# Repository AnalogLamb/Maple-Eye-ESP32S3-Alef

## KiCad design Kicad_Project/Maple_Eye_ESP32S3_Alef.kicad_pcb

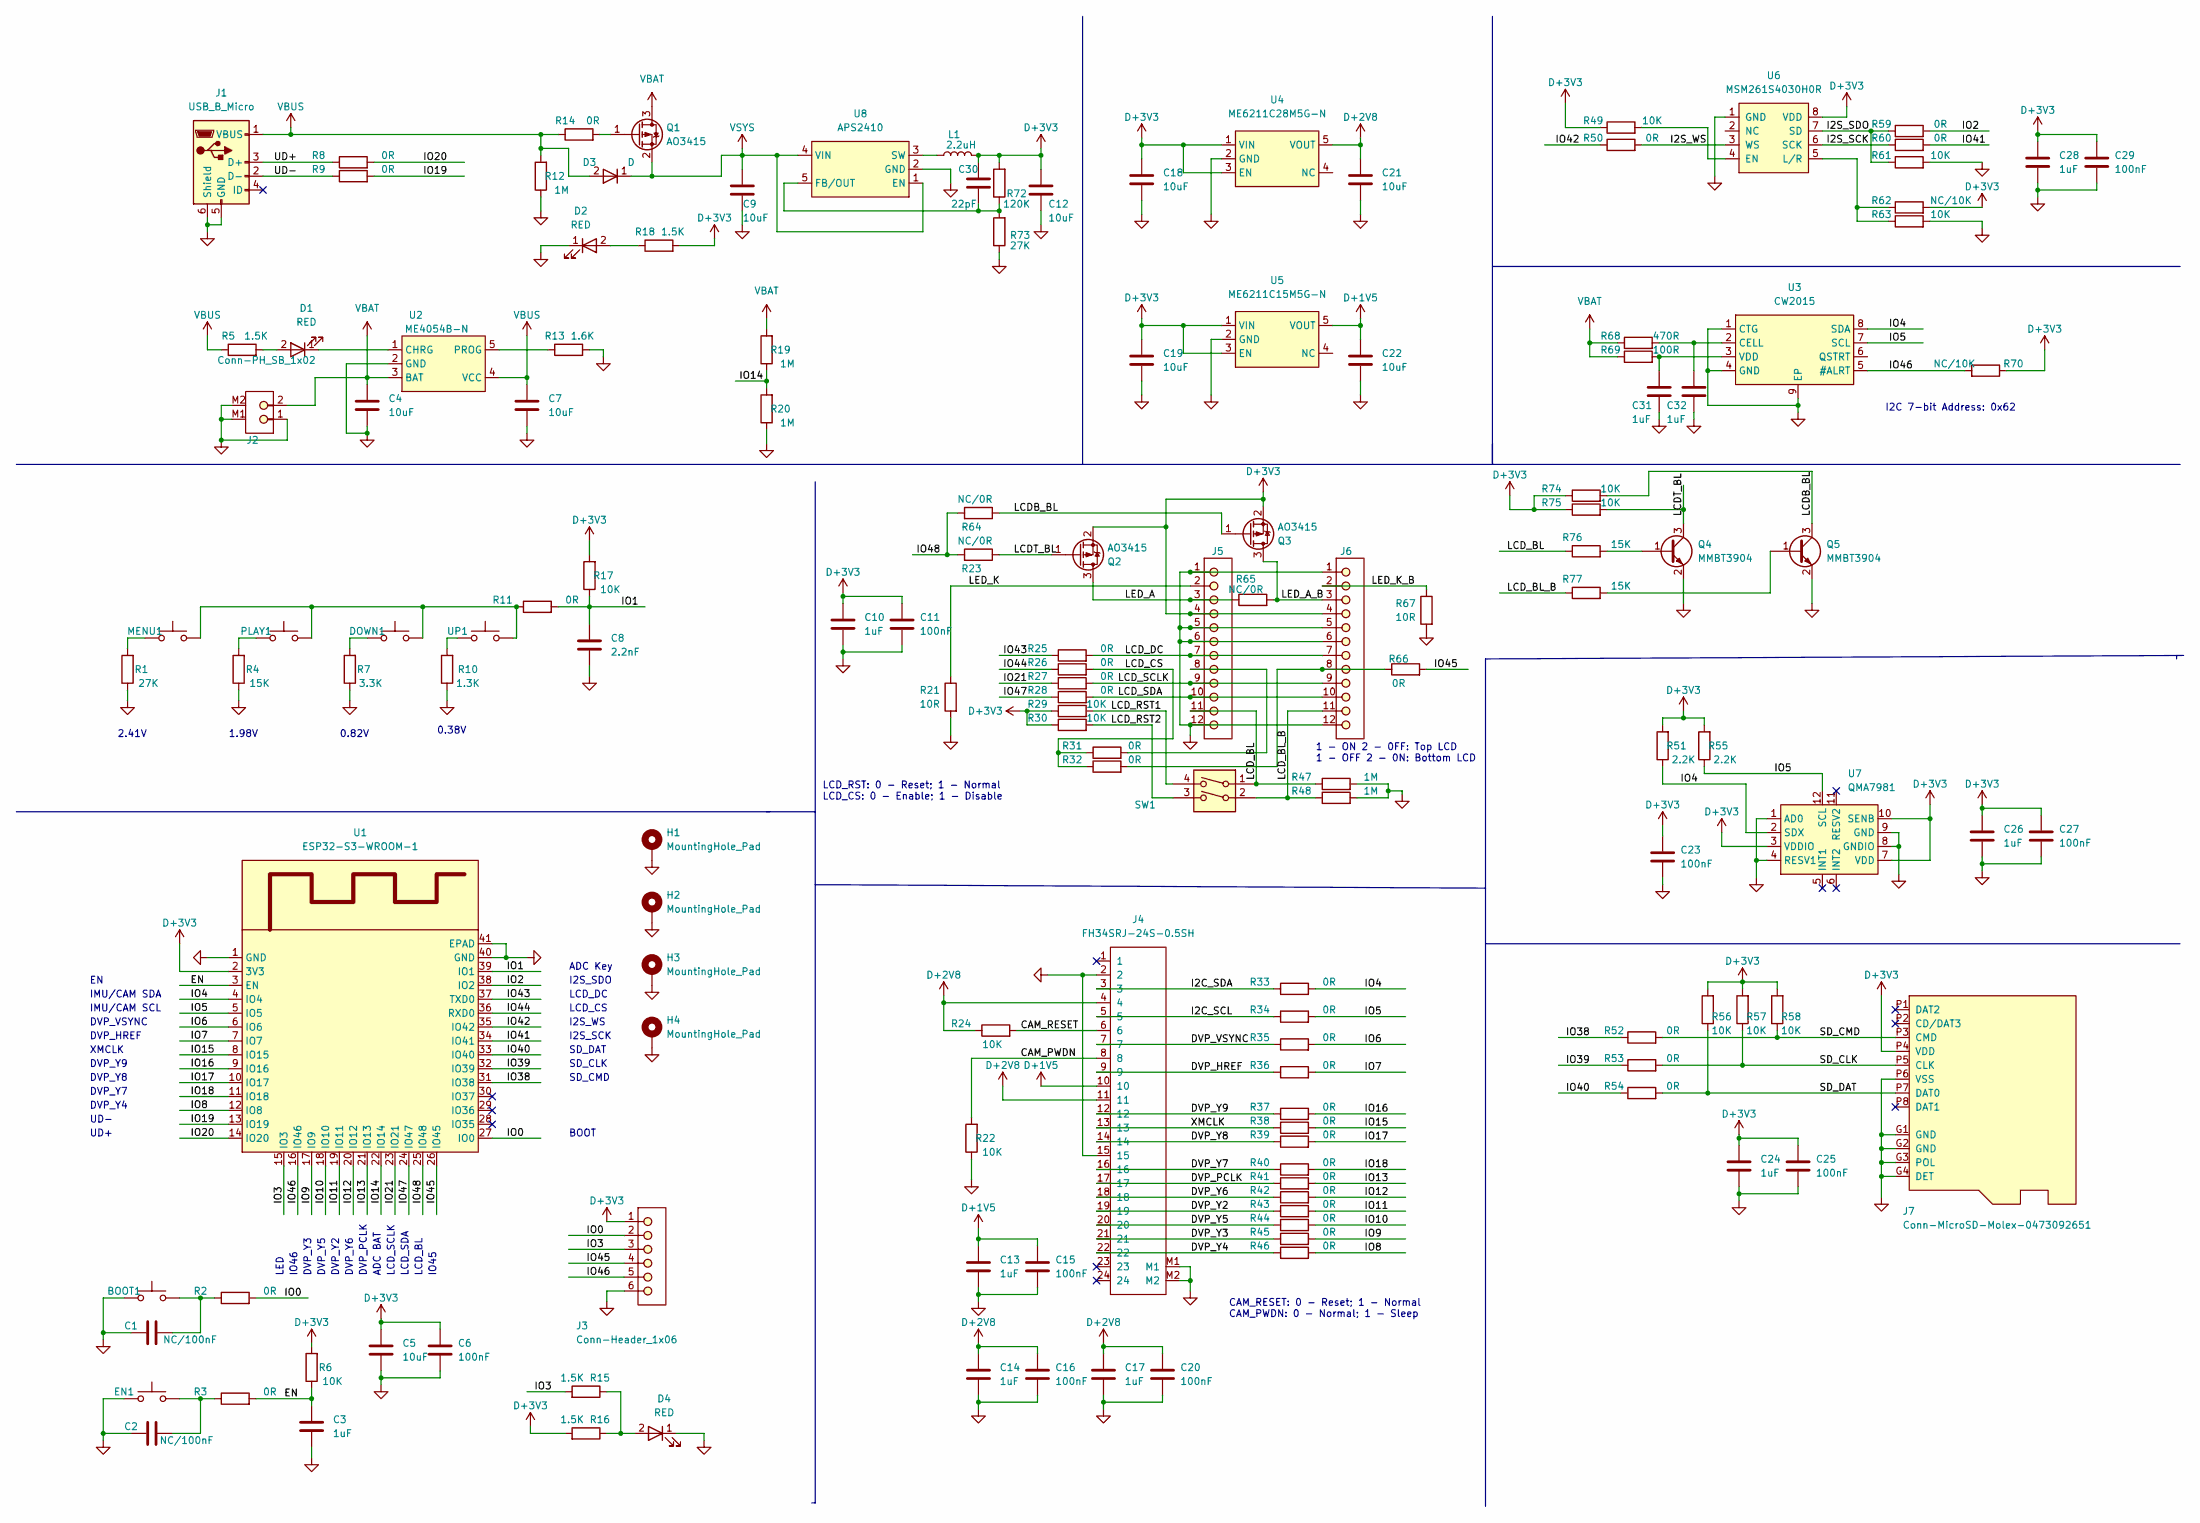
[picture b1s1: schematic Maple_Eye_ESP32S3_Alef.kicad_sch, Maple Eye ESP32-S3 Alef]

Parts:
BOOT1: SW_Push; PB_3x4MM_2P
C1, C2: NC/100nF; 0402C
C3, C10, C13, C14, C17, C24, C26, C28, C31, C32: 1uF; 0402C
C4, C5, C7, C9, C12, C18, C19, C21, C22: 10uF; 0402C
C6, C11, C15, C16, C20, C23, C25, C27, C29: 100nF; 0402C
C8: 2.2nF; 0402C
C30: 22pF; 0402C
D1, D2, D4: RED; 0402D
D3: D; SOD-123
DOWN1: SW_Push; PB_3X4MM_2P_HS
EN1: SW_Push; PB_3x4MM_2P
H1, H2, H3, H4: MountingHole_Pad; MountingHole_2.2mm_M2_Pad_Via
J1: USB_B_Micro; MICRO-USB5+4P-SMD-0.65-B
J2: Conn-PH_SB_1x02; S2B-PH
J3: Conn-Header_1x06; 1X06
J4: FH34SRJ-24S-0.5SH; Conn-FPC-HRS-FH34SRJ-24S-0.5SH
J5, J6: Conn-Header_1x12; LCD_1.3_SPI
J7: Conn-MicroSD-Molex-0473092651
L1: 2.2uH; L_1008_2520Metric
MENU1: SW_Push; PB_3X4MM_2P_HS
PLAY1: SW_Push; PB_3X4MM_2P_HS
Q1, Q2, Q3: AO3415; SOT23-3
Q4, Q5: MMBT3904; SOT23-3
R1, R73: 27K; 0402R
R2, R3, R8, R9, R11, R14, R25, R26, R27, R28, R31, R32, R33, R34, R35, R36, R37, R38, R39, R40, R41, R42, R43, R44, R45, R46, R50, R52, R53, R54, R59, R60, R66: 0R; 0402R
R4, R76, R77: 15K; 0402R
R5, R15, R16, R18: 1.5K; 0402R
R6, R17, R22, R24, R29, R30, R49, R56, R57, R58, R61, R63, R74, R75: 10K; 0402R
R7: 3.3K; 0402R
R10: 1.3K; 0402R
R12, R19, R20, R47, R48: 1M; 0402R
R13: 1.6K; 0402R
R21, R67: 10R; 0603
R23, R64, R65: NC/0R; 0402R
R51, R55: 2.2K; 0402R
R62, R70: NC/10K; 0402R
R68: 470R; 0402R
R69: 100R; 0402R
R72: 120K; 0402R
SW1: SW_DIP_x02; CHS-02B
U1: ESP32-S3-WROOM-1
U2: ME4054B-N; SOT23-5
U3: CW2015; TDFN-8-1EP_3x2mm_P0.5mm_EP1.4x1.4mm
U4: ME6211C28M5G-N; SOT23-5
U5: ME6211C15M5G-N; SOT23-5
U6: MSM261S4030H0R
U7: QMA7981; LGA-12_2x2mm_P0.5mm
U8: APS2410; SOT23-5
UP1: SW_Push; PB_3X4MM_2P_HS

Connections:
+1V5: C13.1, C15.1, C22.1, J4.10, U5.5 (VOUT)
+2V8: C14.1, C16.1, C17.1, C20.1, C21.1, J4.4, J4.11, R24.1, U4.5 (VOUT)
+3V3: C5.1, C6.1, C10.1, C11.1, C12.1, C18.1, C19.1, C23.1, C24.1, C25.1, C26.1, C27.1, C28.1, C29.1, C30.1, J3.1, J5.4, J6.4, J7.P4 (VDD), L1.2, Q2.2 (S), Q3.2 (S), R6.2, R16.2, R17.2, R18.2, R29.1, R30.1, R49.1, R51.2, R55.2, R56.2, R57.2, R58.2, R62.2, R70.1, R72.2, R74.1, R75.1, U1.2 (3V3), U4.1 (VIN), U4.3 (EN), U5.1 (VIN), U5.3 (EN), U6.8 (VDD), U7.3 (VDDIO), U7.7 (VDD), U7.10 (SENB)
/CAM_PWDN: J4.8, R22.2
/CAM_RESET: J4.6, R24.2
/DVP_HREF: J4.9, R36.1
/DVP_PCLK: J4.17, R41.1
/DVP_VSYNC: J4.7, R35.1
/DVP_Y2: J4.19, R43.1
/DVP_Y3: J4.21, R45.1
/DVP_Y4: J4.22, R46.1
/DVP_Y5: J4.20, R44.1
/DVP_Y6: J4.18, R42.1
/DVP_Y7: J4.16, R40.1
/DVP_Y8: J4.14, R39.1
/DVP_Y9: J4.12, R37.1
/EN: C3.1, R3.2, R6.1, U1.3 (EN)
/I2C_SCL: J4.5, R34.1
/I2C_SDA: J4.3, R33.1
/I2S_SCK: R60.1, U6.6 (SCK)
/I2S_SDO: R59.1, R61.1, U6.7 (SD)
/I2S_WS: R50.2, U6.3 (WS)
/IO0: J3.2, R2.2, U1.27 (IO0)
/IO1: C8.1, R11.2, R17.1, U1.39 (IO1)
/IO2: R59.2, U1.38 (IO2)
/IO3: J3.3, R15.2, U1.15 (IO3)
/IO4: R33.2, R51.1, U1.4 (IO4), U3.8 (SDA), U7.2 (SDX)
/IO5: R34.2, R55.1, U1.5 (IO5), U3.7 (SCL), U7.12 (SCL)
/IO6: R35.2, U1.6 (IO6)
/IO7: R36.2, U1.7 (IO7)
/IO8: R46.2, U1.12 (IO8)
/IO9: R45.2, U1.17 (IO9)
/IO10: R44.2, U1.18 (IO10)
/IO11: R43.2, U1.19 (IO11)
/IO12: R42.2, U1.20 (IO12)
/IO13: R41.2, U1.21 (IO13)
/IO14: R19.1, R20.2, U1.22 (IO14)
/IO15: R38.2, U1.8 (IO15)
/IO16: R37.2, U1.9 (IO16)
/IO17: R39.2, U1.10 (IO17)
/IO18: R40.2, U1.11 (IO18)
/IO19: R9.2, U1.13 (IO19)
/IO20: R8.2, U1.14 (IO20)
/IO21: R27.1, U1.23 (IO21)
/IO38: R52.1, U1.31 (IO38)
/IO39: R53.1, U1.32 (IO39)
/IO40: R54.1, U1.33 (IO40)
/IO41: R60.2, U1.34 (IO41)
/IO42: R50.1, U1.35 (IO42)
/IO43: R25.1, U1.37 (TXD0)
/IO44: R26.1, U1.36 (RXD0)
/IO45: J3.4, R66.2, U1.26 (IO45)
/IO46: J3.5, R70.2, U1.16 (IO46), U3.5 (#ALRT)
/IO47: R28.1, U1.24 (IO47)
/IO48: R23.2, R64.2, U1.25 (IO48)
/LCDB_BL: Q3.1 (G), Q5.3 (C), R64.1, R74.2
/LCDT_BL: Q2.1 (G), Q4.3 (C), R23.1, R75.2
/LCD_BL: J5.11, R47.1, R76.1, SW1.1
/LCD_BL_B: J6.11, R48.1, R77.1, SW1.2
/LCD_CS: R26.2, R31.1, R32.1
/LCD_DC: J5.7, J6.7, R25.2
/LCD_RST1: R29.2, SW1.4
/LCD_RST2: R30.2, SW1.3
/LCD_SCLK: J5.9, J6.9, R27.2
/LCD_SDA: J5.10, J6.10, R28.2
/LED_A: J5.3, Q2.3 (D), R65.1
/LED_A_B: J6.3, Q3.3 (D), R65.2
/LED_K: J5.2, R21.1
/LED_K_B: J6.2, R67.1
/SD_CLK: J7.P5 (CLK), R53.2, R57.1
/SD_CMD: J7.P3 (CMD), R52.2, R58.1
/SD_DAT: J7.P7 (DAT0), R54.2, R56.1
/UD+: J1.3 (D+), R8.1
/UD-: J1.2 (D-), R9.1
/XMCLK: J4.13, R38.1
GND: BOOT1.1, C1.1, C2.1, C3.2, C4.2, C5.2, C6.2, C7.2, C8.2, C9.2, C10.2, C11.2, C12.2, C13.2, C14.2, C15.2, C16.2, C17.2, C18.2, C19.2, C20.2, C21.2, C22.2, C23.2, C24.2, C25.2, C26.2, C27.2, C28.2, C29.2, C31.2, C32.2, D2.1 (K), D4.1 (K), EN1.1, H1.1, H2.1, H3.1, H4.1, J1.5 (GND), J1.6 (Shield), J2.1, J2.M1, J2.M2, J3.6, J4.2, J4.15, J4.M1, J4.M2, J5.1, J5.5, J5.6, J5.12, J6.1, J6.5, J6.6, J6.12, J7.G1 (GND), J7.G2 (GND), J7.G3 (POL), J7.G4 (DET), J7.P6 (VSS), Q4.2 (E), Q5.2 (E), R1.1, R4.1, R7.1, R10.1, R12.1, R13.2, R20.1, R21.2, R22.1, R47.2, R48.2, R61.2, R63.2, R67.2, R73.1, U1.1 (GND), U1.40 (GND), U1.41 (EPAD), U2.2 (GND), U3.1 (CTG), U3.4 (GND), U3.9 (EP), U4.2 (GND), U5.2 (GND), U6.1 (GND), U7.1 (AD0), U7.4 (RESV1), U7.8 (GNDIO), U7.9 (GND), U8.2 (GND)
unnamed: BOOT1.2, C1.2, R2.1
unnamed: C2.2, EN1.2, R3.1
unnamed: C30.2, R72.1, R73.2, U8.5 (FB/OUT)
unnamed: C31.1, R69.2, U3.3 (VDD)
unnamed: C32.1, R68.2, U3.2 (CELL)
unnamed: D1.1 (K), U2.1 (CHRG)
unnamed: D1.2 (A), R5.2
unnamed: D2.2 (A), R18.1
unnamed: D4.2 (A), R15.1, R16.1
unnamed: DOWN1.1, R7.2
unnamed: DOWN1.2, MENU1.2, PLAY1.2, R11.1, UP1.2
unnamed: J5.8, R31.2
unnamed: J6.8, R32.2, R66.1
unnamed: L1.1, U8.3 (SW)
unnamed: MENU1.1, R1.2
unnamed: PLAY1.1, R4.2
unnamed: Q1.1 (G), R14.2
unnamed: Q4.1 (B), R76.2
unnamed: Q5.1 (B), R77.2
unnamed: R10.2, UP1.1
unnamed: R13.1, U2.5 (PROG)
unnamed: R49.2, U6.4 (EN)
unnamed: R62.1, R63.1, U6.5 (L/R)
VBAT: C4.1, J2.2, Q1.3 (D), R19.2, R68.1, R69.1, U2.3 (BAT)
VBUS: C7.1, D3.2 (A), J1.1 (VBUS), R5.1, R12.2, R14.1, U2.4 (VCC)
VSYS: C9.1, D3.1 (K), Q1.2 (S), U8.1 (EN), U8.4 (VIN)

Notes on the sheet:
DVP_VSYNC
SD_CMD
DVP_Y9
DVP_Y7
DVP_Y4
LCD_DC
0.38V
UD+
1 - ON 2 - 0FF: Top LCD 1 - OFF 2 - 0N: Bottom LCD
BOOT
DVP_HREF
DVP_Y6
DVP_Y8
1.98V
LCD_BL
LCD_SCLK
2.41V
IMU/CAM SCL
CAM_RESET: 0 - Reset; 1 - Normal CAM_PWDN: 0 - Normal; 1 - Sleep
DVP_Y3
DVP_Y2
UD-
DVP_Y5
IO45
I2C 7-bit Address: 0x62
0.82V
SD_CLK
I2S_WS
XMCLK
ADC Key
LED
LCD_RST: 0 - Reset; 1 - Normal LCD_CS: 0 - Enable; 1 - Disable
I2S_SCK
DVP_PCLK
LCD_CS
LCD_SDA
ADC BAT
IMU/CAM SDA
I2S_SDO
IO46

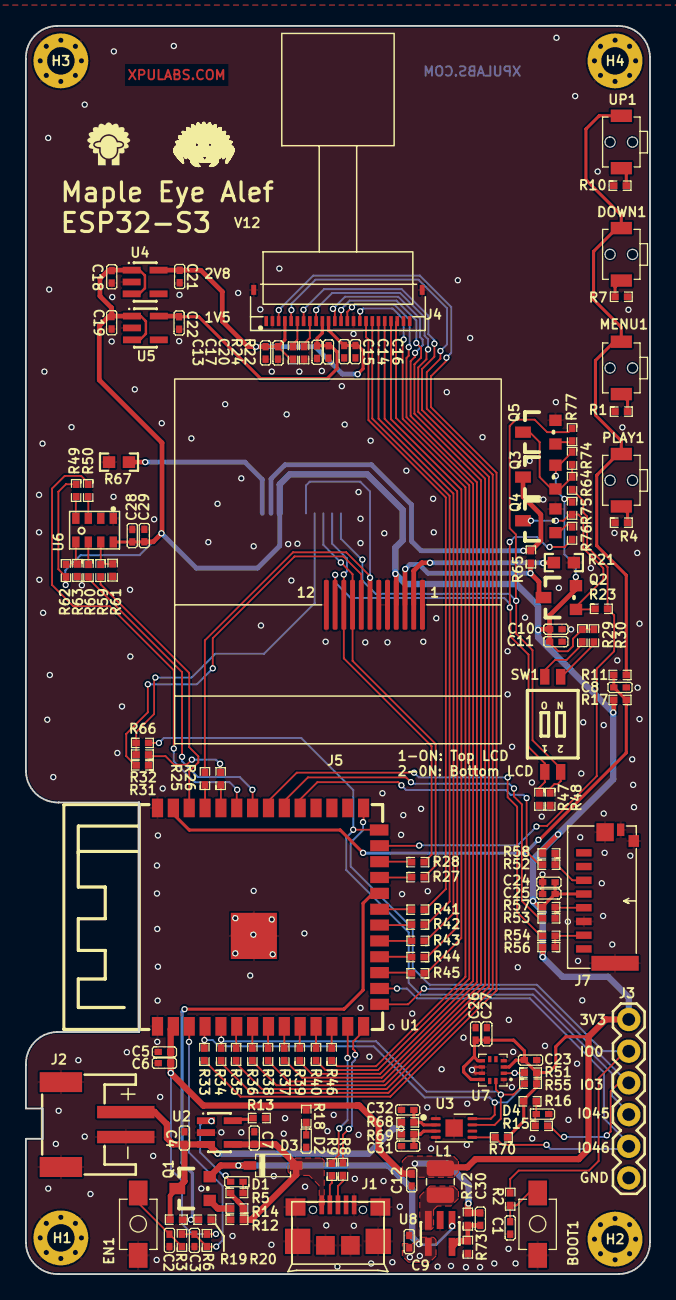
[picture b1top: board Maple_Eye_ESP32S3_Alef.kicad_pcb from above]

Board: 2 copper layers, 50.0 x 100.0 mm, 144 parts (1 on the bottom side), 102 nets.
